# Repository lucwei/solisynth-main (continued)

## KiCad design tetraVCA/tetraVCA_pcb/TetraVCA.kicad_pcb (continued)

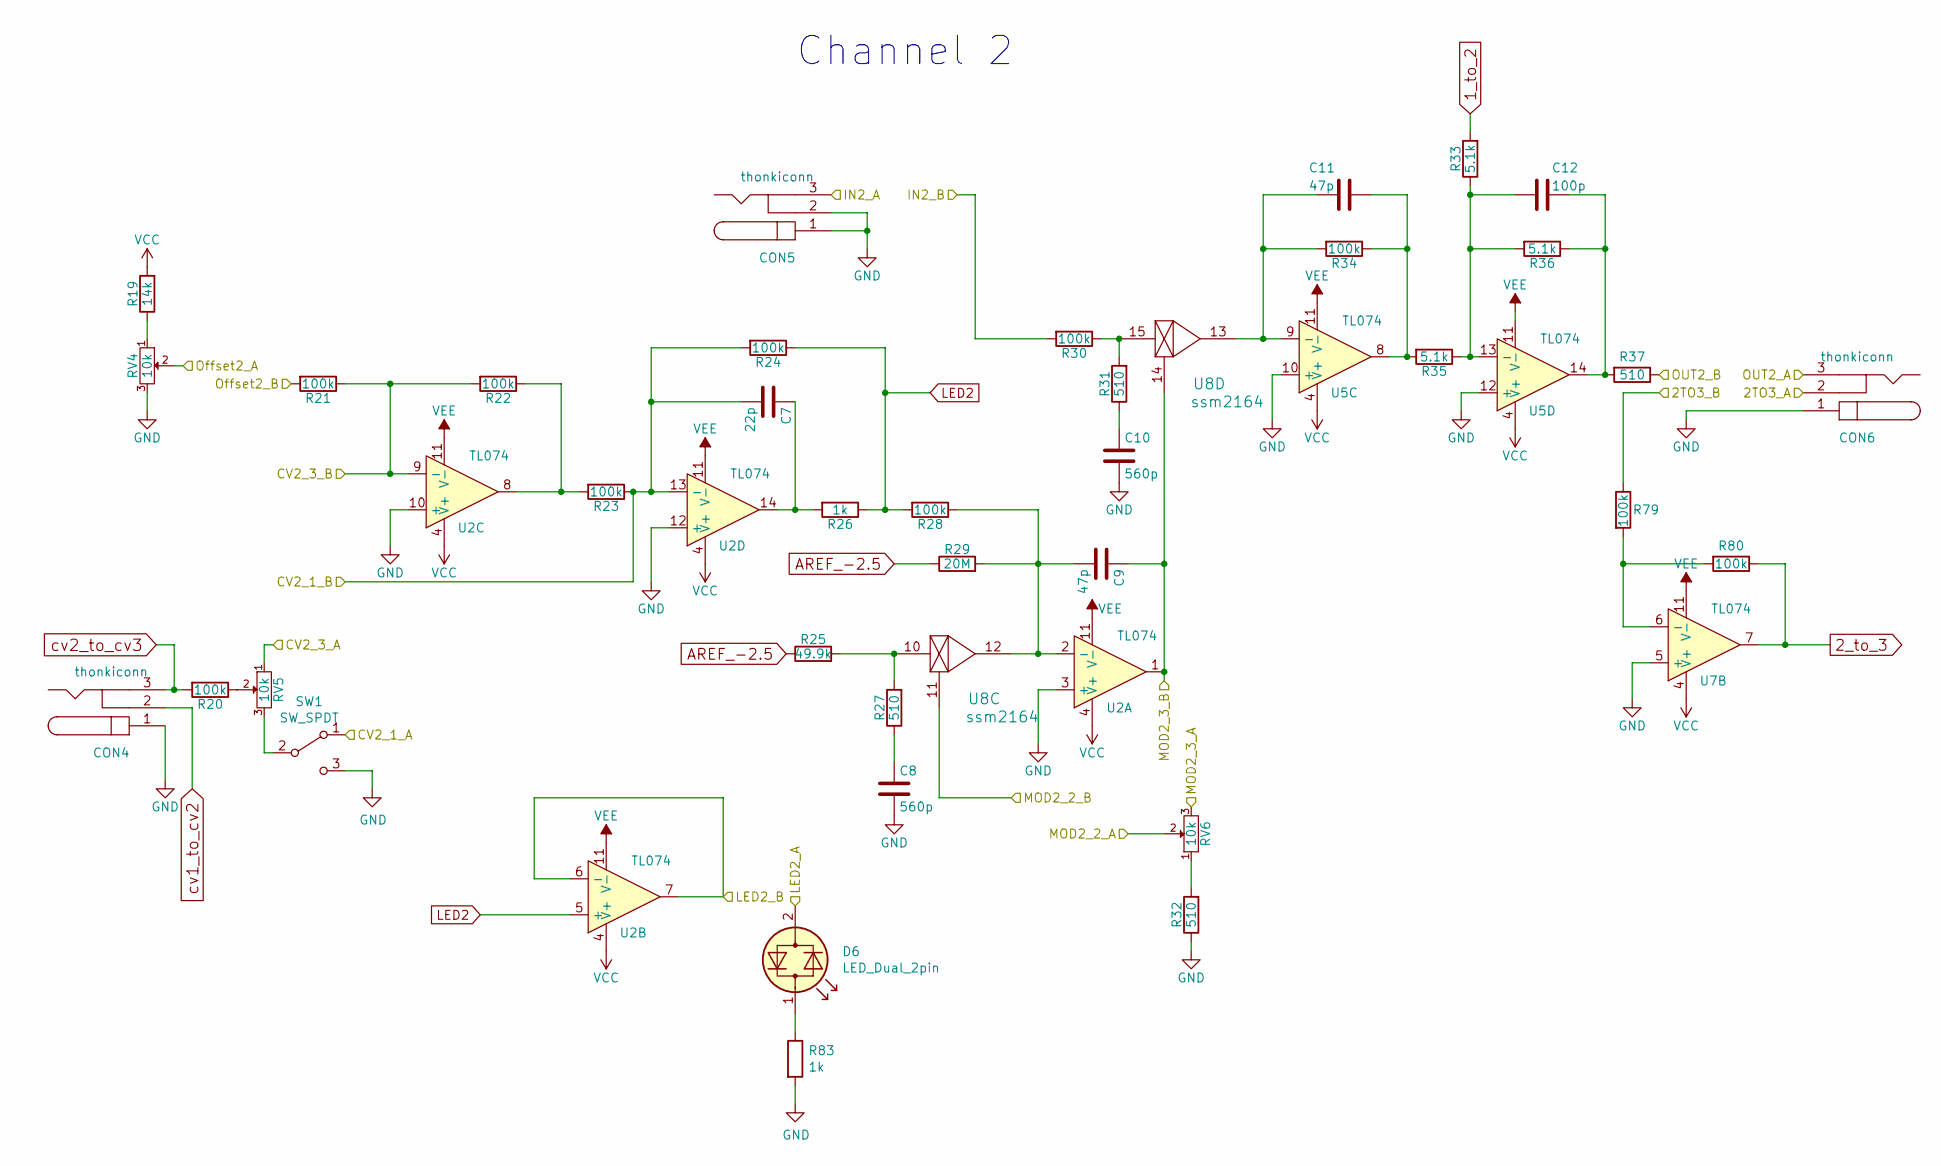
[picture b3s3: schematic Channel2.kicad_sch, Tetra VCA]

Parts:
C7: 22p; C_0603_1608Metric_Pad1.05x0.95mm_HandSolder
C8, C10: 560p; C_0603_1608Metric_Pad1.05x0.95mm_HandSolder
C9, C11: 47p; C_0603_1608Metric_Pad1.05x0.95mm_HandSolder
C12: 100p; C_0603_1608Metric_Pad1.05x0.95mm_HandSolder
CON4, CON5, CON6: thonkiconn; MPN PJ398SM
D6: LED_Dual_2pin; LED_D3.0mm; MPN LTL-10CHJ
R19: 14k; R_0603_1608Metric_Pad1.05x0.95mm_HandSolder
R20, R21, R22, R23, R24, R28, R30, R34, R79, R80: 100k; R_0603_1608Metric_Pad1.05x0.95mm_HandSolder
R25: 49.9k; R_0603_1608Metric_Pad1.05x0.95mm_HandSolder
R26, R83: 1k; R_0603_1608Metric_Pad1.05x0.95mm_HandSolder
R27, R31, R32, R37: 510; R_0603_1608Metric_Pad1.05x0.95mm_HandSolder
R29: 20M; R_0603_1608Metric_Pad1.05x0.95mm_HandSolder
R33, R35, R36: 5.1k; R_0603_1608Metric_Pad1.05x0.95mm_HandSolder
RV4: 10k; Potentiometer_Alps_RK09K_Single_Vertical; MPN RK09L1140A5E
RV5, RV6: 10k; Potentiometer_Alps_RK09K_Single_Vertical; MPN PTV09A-4025U-B103
SW1: SW_SPDT; Switch_EG1249; MPN EG1248
U2, U5, U7: TL074; SOIC-14_3.9x8.7mm_P1.27mm; MPN TL074
U8: ssm2164; SOIC-16_3.9x9.9mm_P1.27mm; MPN SSM2164

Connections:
1_to_2: R33.2; also elsewhere on the board
2TO3_A: CON6.2; also elsewhere on the board
2TO3_B: R79.1; also elsewhere on the board
2_to_3: R80.1, U7.7; also elsewhere on the board
AREF_-2.5: R25.1, R29.1; also elsewhere on the board
CV2_1_A: SW1.1 (A); also elsewhere on the board
CV2_1_B: C7.2, R23.1, R24.2, U2.13 (-); also elsewhere on the board
CV2_3_A: RV5.1; also elsewhere on the board
CV2_3_B: R21.1, R22.2, U2.9 (-); also elsewhere on the board
GND: C8.2, C10.2, CON4.1, CON5.1, CON5.2, CON6.1, R32.1, R83.2, RV4.3, SW1.3 (C), U2.3 (+), U2.10 (+), U2.12 (+), U5.10 (+), U5.12 (+), U7.5 (+); also elsewhere on the board
IN2_A: CON5.3; also elsewhere on the board
IN2_B: R30.2; also elsewhere on the board
LED2: R24.1, R26.1, R28.2, U2.5 (+)
LED2_A: D6.2 (AK); also elsewhere on the board
LED2_B: U2.6 (-), U2.7; also elsewhere on the board
MOD2_2_A: RV6.2; also elsewhere on the board
MOD2_2_B: U8.11; also elsewhere on the board
MOD2_3_A: RV6.3; also elsewhere on the board
MOD2_3_B: C9.1, U2.1, U8.14; also elsewhere on the board
unnamed: C7.1, R26.2, U2.14
unnamed: C8.1, R27.1
unnamed: C9.2, R28.1, R29.2, U2.2 (-), U8.12
unnamed: C10.1, R31.1
unnamed: C11.1, R34.1, R35.2, U5.8
unnamed: C11.2, R34.2, U5.9 (-), U8.13
unnamed: C12.1, R36.1, R37.2, U5.14
unnamed: C12.2, R33.1, R35.1, R36.2, U5.13 (-)
unnamed: D6.1 (KA), R83.1
unnamed: R19.1, RV4.1
unnamed: R20.1, RV5.2
unnamed: R22.1, R23.2, U2.8
unnamed: R25.2, R27.2, U8.10
unnamed: R30.1, R31.2, U8.15
unnamed: R32.2, RV6.1
unnamed: R79.2, R80.2, U7.6 (-)
unnamed: RV5.3, SW1.2 (B)
OUT2_A: CON6.3; also elsewhere on the board
OUT2_B: R37.1; also elsewhere on the board
Offset2_A: RV4.2; also elsewhere on the board
Offset2_B: R21.2; also elsewhere on the board
VCC: R19.2, U2.4 (V+), U5.4 (V+), U7.4 (V+); also elsewhere on the board
VEE: U2.11 (V-), U5.11 (V-), U7.11 (V-); also elsewhere on the board
cv1_to_cv2: CON4.2; also elsewhere on the board
cv2_to_cv3: CON4.3, R20.2; also elsewhere on the board

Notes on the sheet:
Channel 2

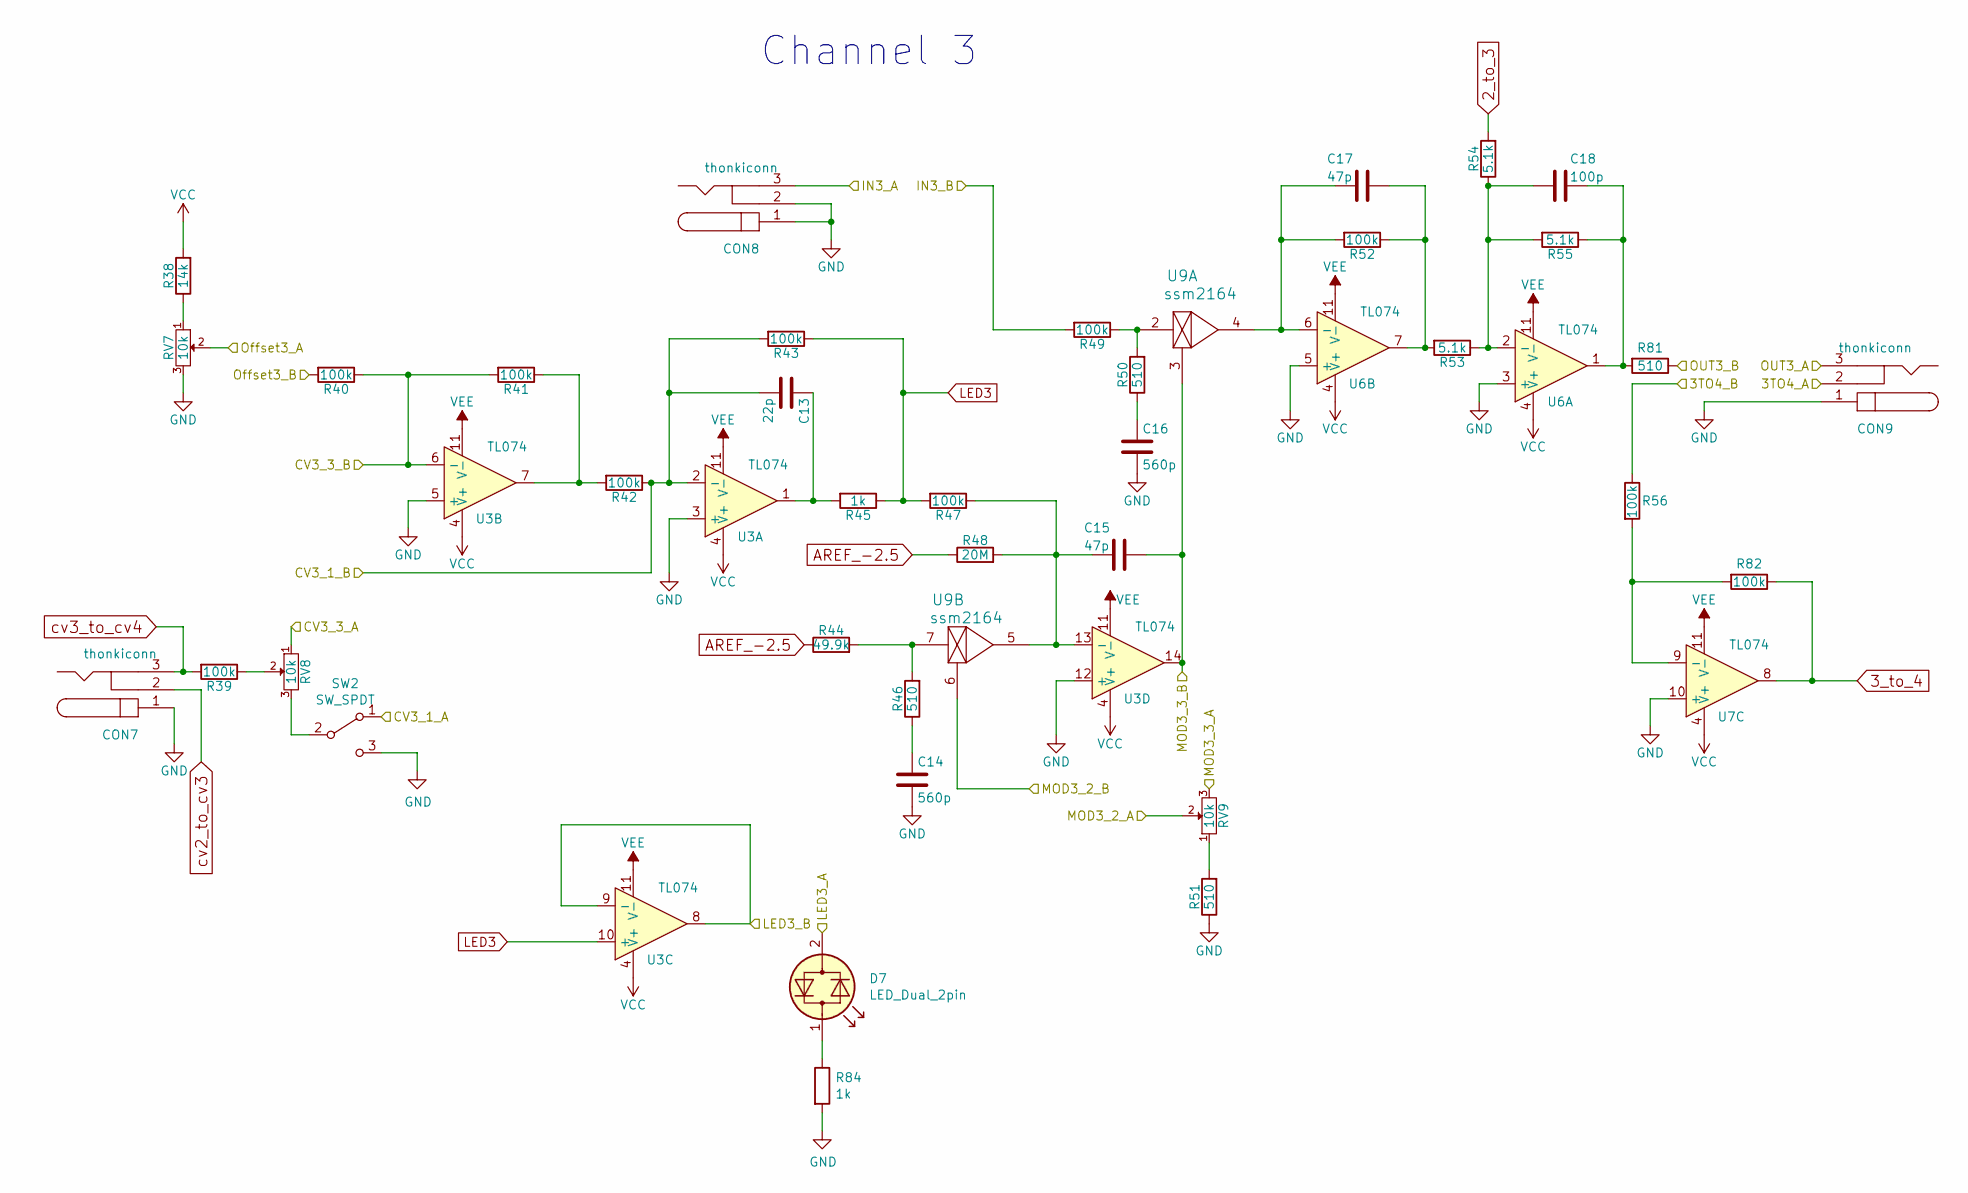
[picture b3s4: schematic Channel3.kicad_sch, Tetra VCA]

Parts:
C13: 22p; C_0603_1608Metric_Pad1.05x0.95mm_HandSolder
C14, C16: 560p; C_0603_1608Metric_Pad1.05x0.95mm_HandSolder
C15, C17: 47p; C_0603_1608Metric_Pad1.05x0.95mm_HandSolder
C18: 100p; C_0603_1608Metric_Pad1.05x0.95mm_HandSolder
CON7, CON8, CON9: thonkiconn; MPN PJ398SM
D7: LED_Dual_2pin; LED_D3.0mm; MPN LTL-10CHJ
R38: 14k; R_0603_1608Metric_Pad1.05x0.95mm_HandSolder
R39, R40, R41, R42, R43, R47, R49, R52, R56, R82: 100k; R_0603_1608Metric_Pad1.05x0.95mm_HandSolder
R44: 49.9k; R_0603_1608Metric_Pad1.05x0.95mm_HandSolder
R45, R84: 1k; R_0603_1608Metric_Pad1.05x0.95mm_HandSolder
R46, R50, R51, R81: 510; R_0603_1608Metric_Pad1.05x0.95mm_HandSolder
R48: 20M; R_0603_1608Metric_Pad1.05x0.95mm_HandSolder
R53, R54, R55: 5.1k; R_0603_1608Metric_Pad1.05x0.95mm_HandSolder
RV7: 10k; Potentiometer_Alps_RK09K_Single_Vertical; MPN RK09L1140A5E
RV8, RV9: 10k; Potentiometer_Alps_RK09K_Single_Vertical; MPN PTV09A-4025U-B103
SW2: SW_SPDT; Switch_EG1249; MPN EG1248
U3, U6, U7: TL074; SOIC-14_3.9x8.7mm_P1.27mm; MPN TL074
U9: ssm2164; SOIC-16_3.9x9.9mm_P1.27mm; MPN SSM2164

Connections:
2_to_3: R54.2; also elsewhere on the board
3TO4_A: CON9.2; also elsewhere on the board
3TO4_B: R56.1; also elsewhere on the board
3_to_4: R82.1, U7.8; also elsewhere on the board
AREF_-2.5: R44.1, R48.1; also elsewhere on the board
CV3_1_A: SW2.1 (A); also elsewhere on the board
CV3_1_B: C13.2, R42.1, R43.2, U3.2 (-); also elsewhere on the board
CV3_3_A: RV8.1; also elsewhere on the board
CV3_3_B: R40.1, R41.2, U3.6 (-); also elsewhere on the board
GND: C14.2, C16.2, CON7.1, CON8.1, CON8.2, CON9.1, R51.1, R84.2, RV7.3, SW2.3 (C), U3.3 (+), U3.5 (+), U3.12 (+), U6.3 (+), U6.5 (+), U7.10 (+); also elsewhere on the board
IN3_A: CON8.3; also elsewhere on the board
IN3_B: R49.2; also elsewhere on the board
LED3: R43.1, R45.1, R47.2, U3.10 (+)
LED3_A: D7.2 (AK); also elsewhere on the board
LED3_B: U3.8, U3.9 (-); also elsewhere on the board
MOD3_2_A: RV9.2; also elsewhere on the board
MOD3_2_B: U9.6; also elsewhere on the board
MOD3_3_A: RV9.3; also elsewhere on the board
MOD3_3_B: C15.1, U3.14, U9.3; also elsewhere on the board
unnamed: C13.1, R45.2, U3.1
unnamed: C14.1, R46.1
unnamed: C15.2, R47.1, R48.2, U3.13 (-), U9.5
unnamed: C16.1, R50.1
unnamed: C17.1, R52.1, R53.2, U6.7
unnamed: C17.2, R52.2, U6.6 (-), U9.4
unnamed: C18.1, R55.1, R81.2, U6.1
unnamed: C18.2, R53.1, R54.1, R55.2, U6.2 (-)
unnamed: D7.1 (KA), R84.1
unnamed: R38.1, RV7.1
unnamed: R39.1, RV8.2
unnamed: R41.1, R42.2, U3.7
unnamed: R44.2, R46.2, U9.7
unnamed: R49.1, R50.2, U9.2
unnamed: R51.2, RV9.1
unnamed: R56.2, R82.2, U7.9 (-)
unnamed: RV8.3, SW2.2 (B)
OUT3_A: CON9.3; also elsewhere on the board
OUT3_B: R81.1; also elsewhere on the board
Offset3_A: RV7.2; also elsewhere on the board
Offset3_B: R40.2; also elsewhere on the board
VCC: R38.2, U3.4 (V+), U6.4 (V+), U7.4 (V+); also elsewhere on the board
VEE: U3.11 (V-), U6.11 (V-), U7.11 (V-); also elsewhere on the board
cv2_to_cv3: CON7.2; also elsewhere on the board
cv3_to_cv4: CON7.3, R39.2; also elsewhere on the board

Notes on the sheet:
Channel 3

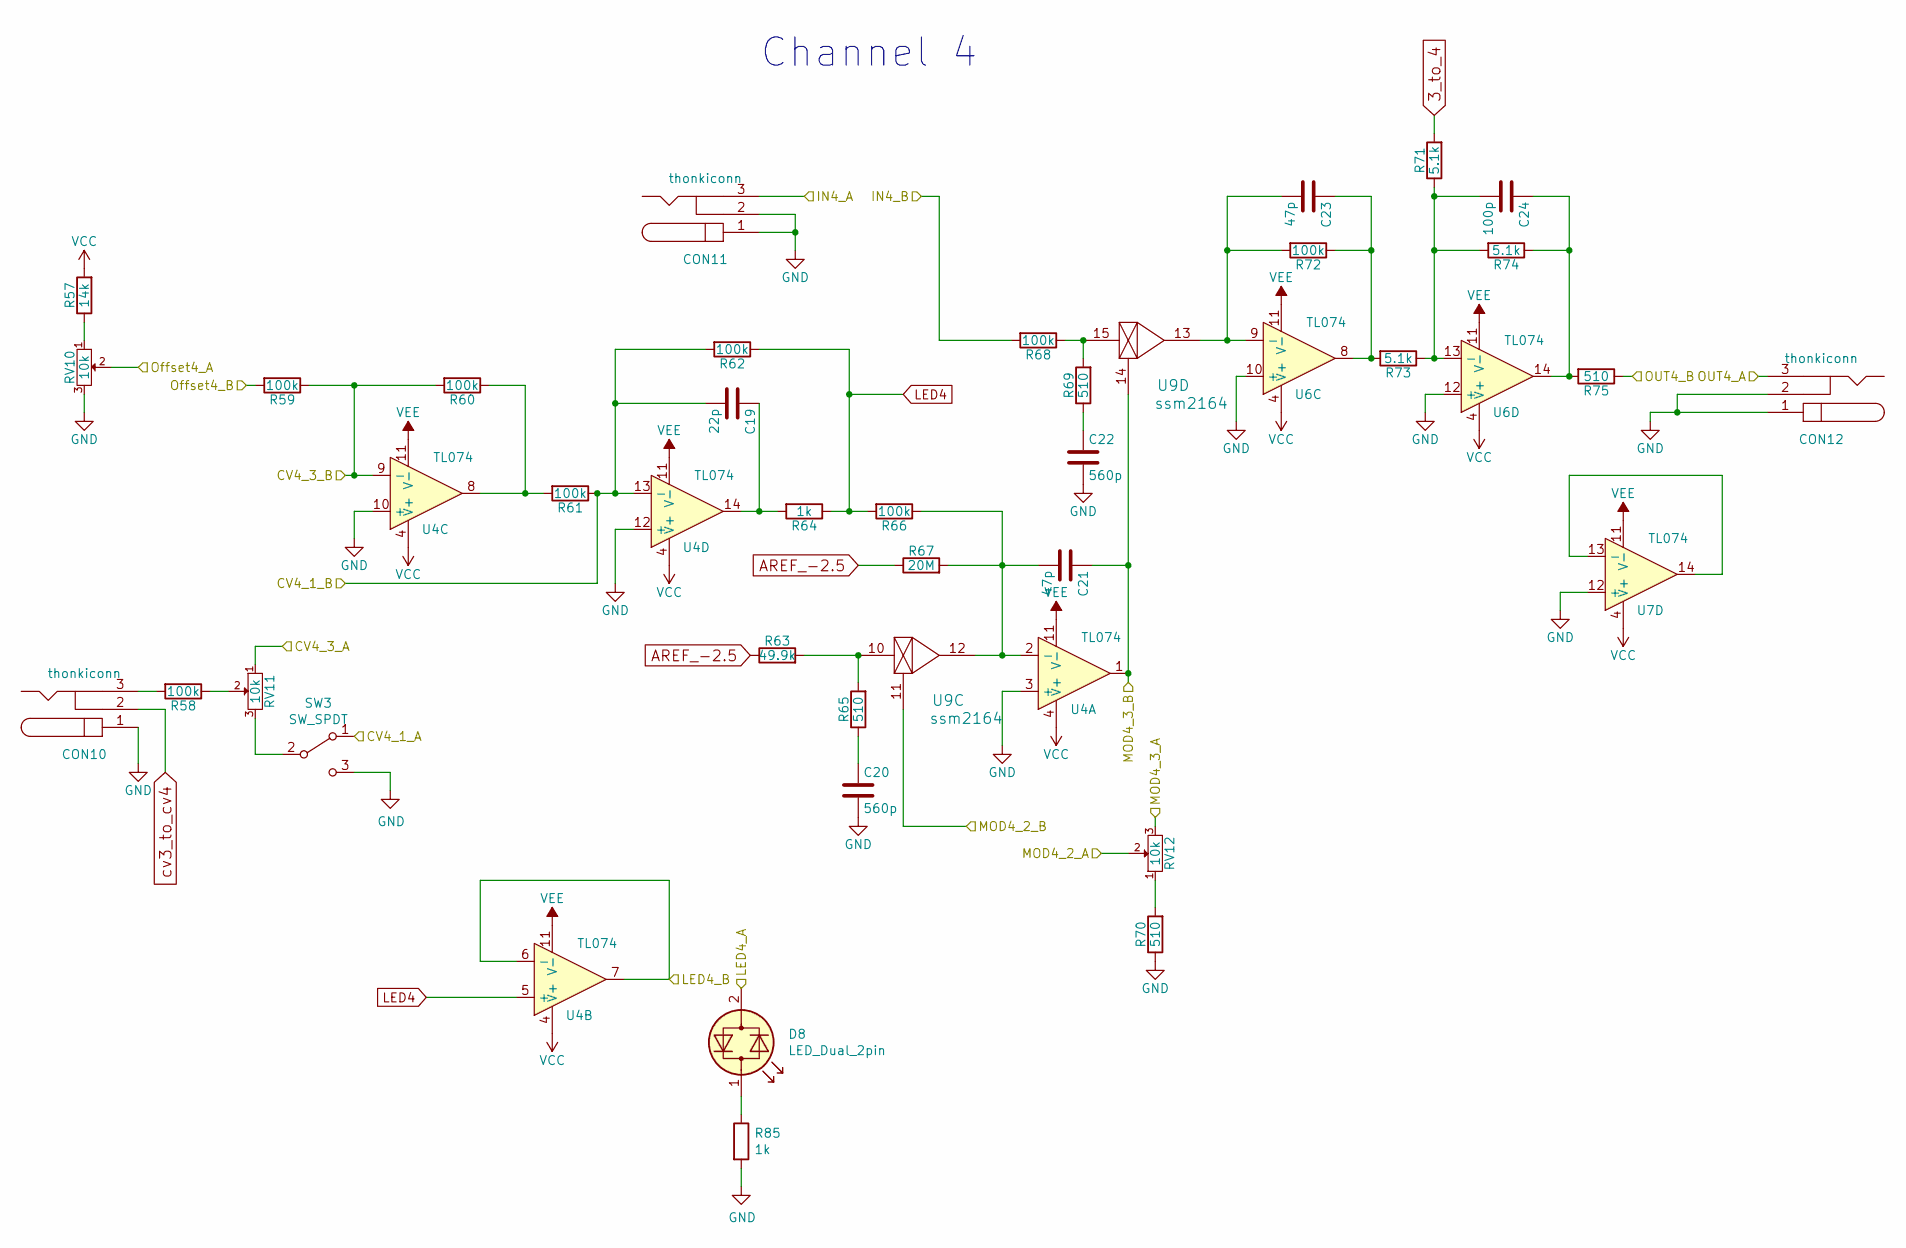
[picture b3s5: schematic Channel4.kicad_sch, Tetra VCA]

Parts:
C19: 22p; C_0603_1608Metric_Pad1.05x0.95mm_HandSolder
C20, C22: 560p; C_0603_1608Metric_Pad1.05x0.95mm_HandSolder
C21, C23: 47p; C_0603_1608Metric_Pad1.05x0.95mm_HandSolder
C24: 100p; C_0603_1608Metric_Pad1.05x0.95mm_HandSolder
CON10, CON11, CON12: thonkiconn; MPN PJ398SM
D8: LED_Dual_2pin; LED_D3.0mm; MPN LTL-10CHJ
R57: 14k; R_0603_1608Metric_Pad1.05x0.95mm_HandSolder
R58, R59, R60, R61, R62, R66, R68, R72: 100k; R_0603_1608Metric_Pad1.05x0.95mm_HandSolder
R63: 49.9k; R_0603_1608Metric_Pad1.05x0.95mm_HandSolder
R64, R85: 1k; R_0603_1608Metric_Pad1.05x0.95mm_HandSolder
R65, R69, R70, R75: 510; R_0603_1608Metric_Pad1.05x0.95mm_HandSolder
R67: 20M; R_0603_1608Metric_Pad1.05x0.95mm_HandSolder
R71, R73, R74: 5.1k; R_0603_1608Metric_Pad1.05x0.95mm_HandSolder
RV10: 10k; Potentiometer_Alps_RK09K_Single_Vertical; MPN RK09L1140A5E
RV11, RV12: 10k; Potentiometer_Alps_RK09K_Single_Vertical; MPN PTV09A-4025U-B103
SW3: SW_SPDT; Switch_EG1249; MPN EG1248
U4, U6, U7: TL074; SOIC-14_3.9x8.7mm_P1.27mm; MPN TL074
U9: ssm2164; SOIC-16_3.9x9.9mm_P1.27mm; MPN SSM2164

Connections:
3_to_4: R71.2; also elsewhere on the board
AREF_-2.5: R63.1, R67.1; also elsewhere on the board
CV4_1_A: SW3.1 (A); also elsewhere on the board
CV4_1_B: C19.2, R61.1, R62.2, U4.13 (-); also elsewhere on the board
CV4_3_A: RV11.1; also elsewhere on the board
CV4_3_B: R59.1, R60.2, U4.9 (-); also elsewhere on the board
GND: C20.2, C22.2, CON10.1, CON11.1, CON11.2, CON12.1, CON12.2, R70.1, R85.2, RV10.3, SW3.3 (C), U4.3 (+), U4.10 (+), U4.12 (+), U6.10 (+), U6.12 (+), U7.12 (+); also elsewhere on the board
IN4_A: CON11.3; also elsewhere on the board
IN4_B: R68.2; also elsewhere on the board
LED4: R62.1, R64.1, R66.2, U4.5 (+)
LED4_A: D8.2 (AK); also elsewhere on the board
LED4_B: U4.6 (-), U4.7; also elsewhere on the board
MOD4_2_A: RV12.2; also elsewhere on the board
MOD4_2_B: U9.11; also elsewhere on the board
MOD4_3_A: RV12.3; also elsewhere on the board
MOD4_3_B: C21.1, U4.1, U9.14; also elsewhere on the board
unnamed: C19.1, R64.2, U4.14
unnamed: C20.1, R65.1
unnamed: C21.2, R66.1, R67.2, U4.2 (-), U9.12
unnamed: C22.1, R69.1
unnamed: C23.1, R72.1, R73.2, U6.8
unnamed: C23.2, R72.2, U6.9 (-), U9.13
unnamed: C24.1, R74.1, R75.2, U6.14
unnamed: C24.2, R71.1, R73.1, R74.2, U6.13 (-)
unnamed: CON10.3, R58.2
unnamed: D8.1 (KA), R85.1
unnamed: R57.1, RV10.1
unnamed: R58.1, RV11.2
unnamed: R60.1, R61.2, U4.8
unnamed: R63.2, R65.2, U9.10
unnamed: R68.1, R69.2, U9.15
unnamed: R70.2, RV12.1
unnamed: RV11.3, SW3.2 (B)
unnamed: U7.13 (-), U7.14
OUT4_A: CON12.3; also elsewhere on the board
OUT4_B: R75.1; also elsewhere on the board
Offset4_A: RV10.2; also elsewhere on the board
Offset4_B: R59.2; also elsewhere on the board
VCC: R57.2, U4.4 (V+), U6.4 (V+), U7.4 (V+); also elsewhere on the board
VEE: U4.11 (V-), U6.11 (V-), U7.11 (V-); also elsewhere on the board
cv3_to_cv4: CON10.2; also elsewhere on the board

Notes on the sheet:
Channel 4

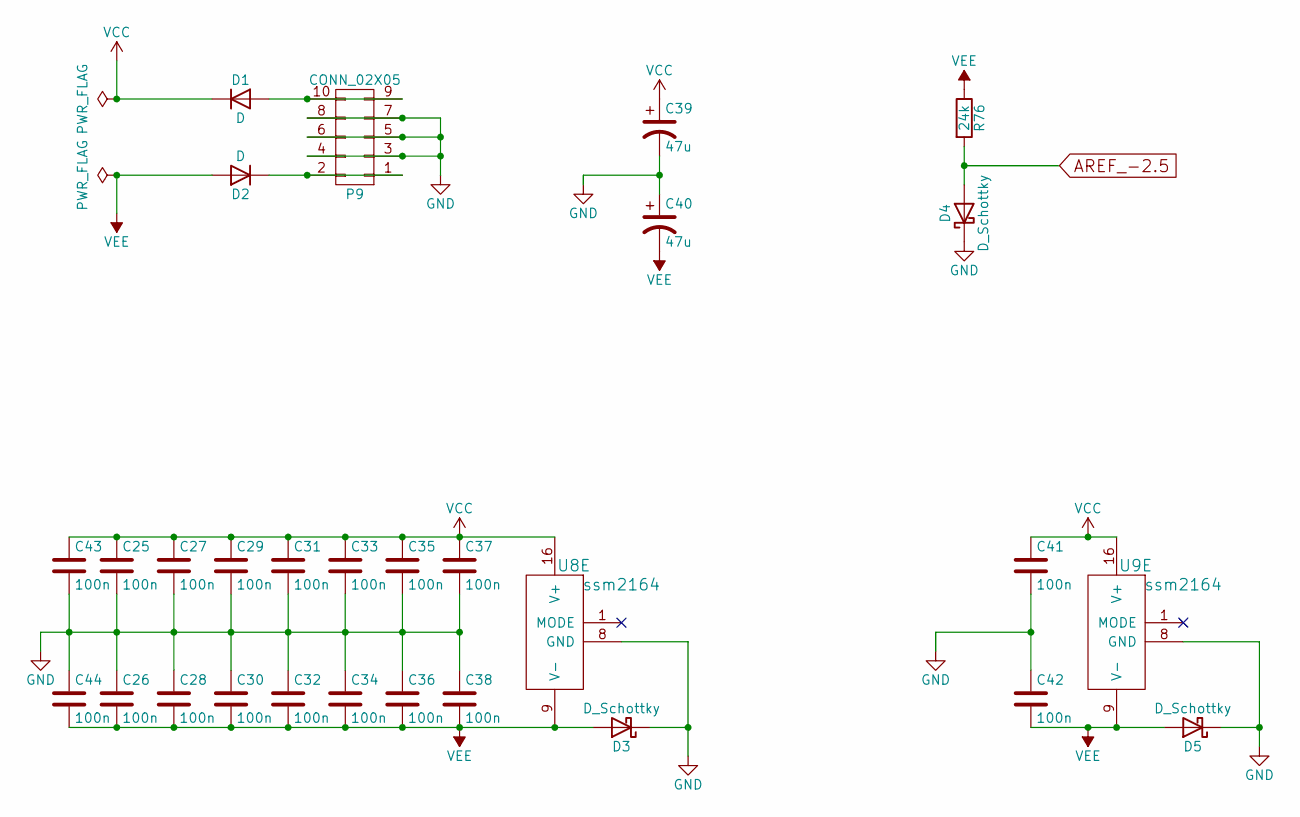
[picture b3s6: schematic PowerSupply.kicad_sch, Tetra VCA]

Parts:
C25, C26, C27, C28, C29, C30, C31, C32, C33, C34, C35, C36, C37, C38, C41, C42, C43, C44: 100n; C_0603_1608Metric_Pad1.05x0.95mm_HandSolder
C39, C40: 47u; CP_Elec_6.3x5.3
D1, D2: D; D_0603_1608Metric_Pad1.05x0.95mm_HandSolder
D3, D5: D_Schottky; D_0603_1608Metric_Pad1.05x0.95mm_HandSolder
D4: D_Schottky; TSOT-23; MPN LM4040CYM3-2.5-TR
P9: CONN_02X05; IDC-Header_2x05_P2.54mm_Vertical; MPN 61201021621
R76: 24k; R_0603_1608Metric_Pad1.05x0.95mm_HandSolder
U8, U9: ssm2164; SOIC-16_3.9x9.9mm_P1.27mm; MPN SSM2164

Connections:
AREF_-2.5: D4.2 (A), R76.2; also elsewhere on the board
GND: C25.2, C26.1, C27.2, C28.1, C29.2, C30.1, C31.2, C32.1, C33.2, C34.1, C35.2, C36.1, C37.2, C38.1, C39.2, C40.1, C41.2, C42.1, C43.2, C44.1, D3.1 (K), D4.1 (K), D5.1 (K), P9.3, P9.4, P9.5, P9.6, P9.7, P9.8, U8.8 (GND), U9.8 (GND); also elsewhere on the board
unnamed: D1.2 (A), P9.9, P9.10
unnamed: D2.1 (K), P9.1, P9.2
VCC: C25.1, C27.1, C29.1, C31.1, C33.1, C35.1, C37.1, C39.1, C41.1, C43.1, D1.1 (K), U8.16 (V+), U9.16 (V+); also elsewhere on the board
VEE: C26.2, C28.2, C30.2, C32.2, C34.2, C36.2, C38.2, C40.2, C42.2, C44.2, D2.2 (A), D3.2 (A), D5.2 (A), R76.1, U8.9 (V-), U9.9 (V-); also elsewhere on the board

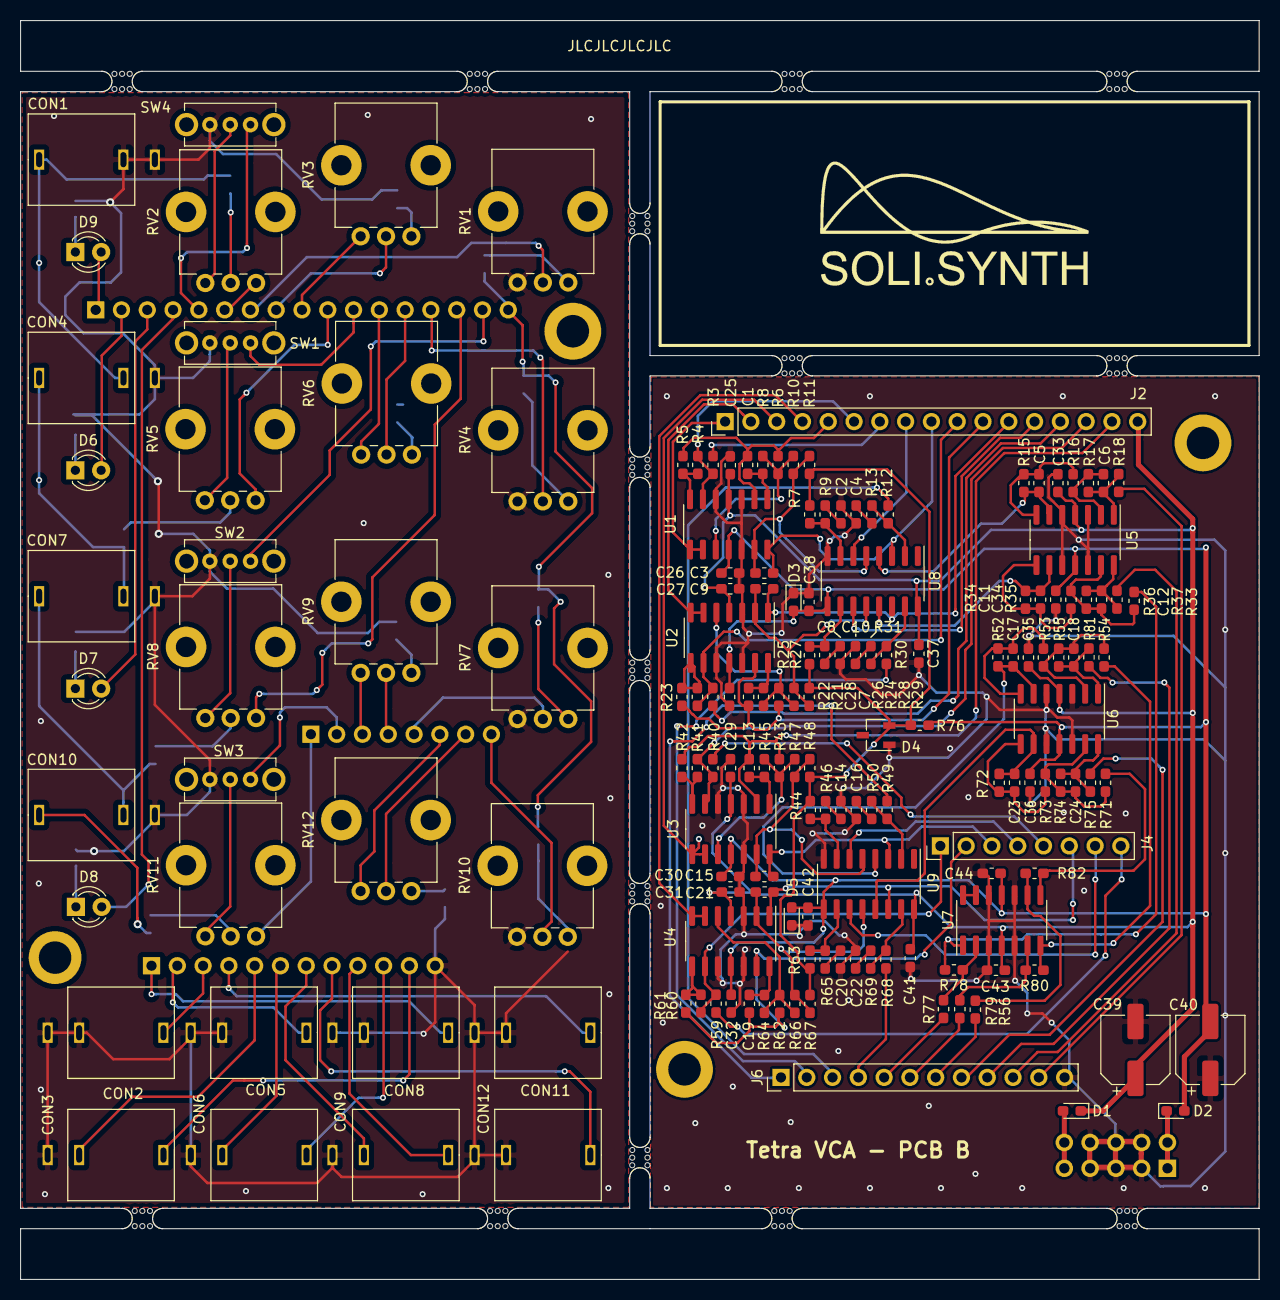
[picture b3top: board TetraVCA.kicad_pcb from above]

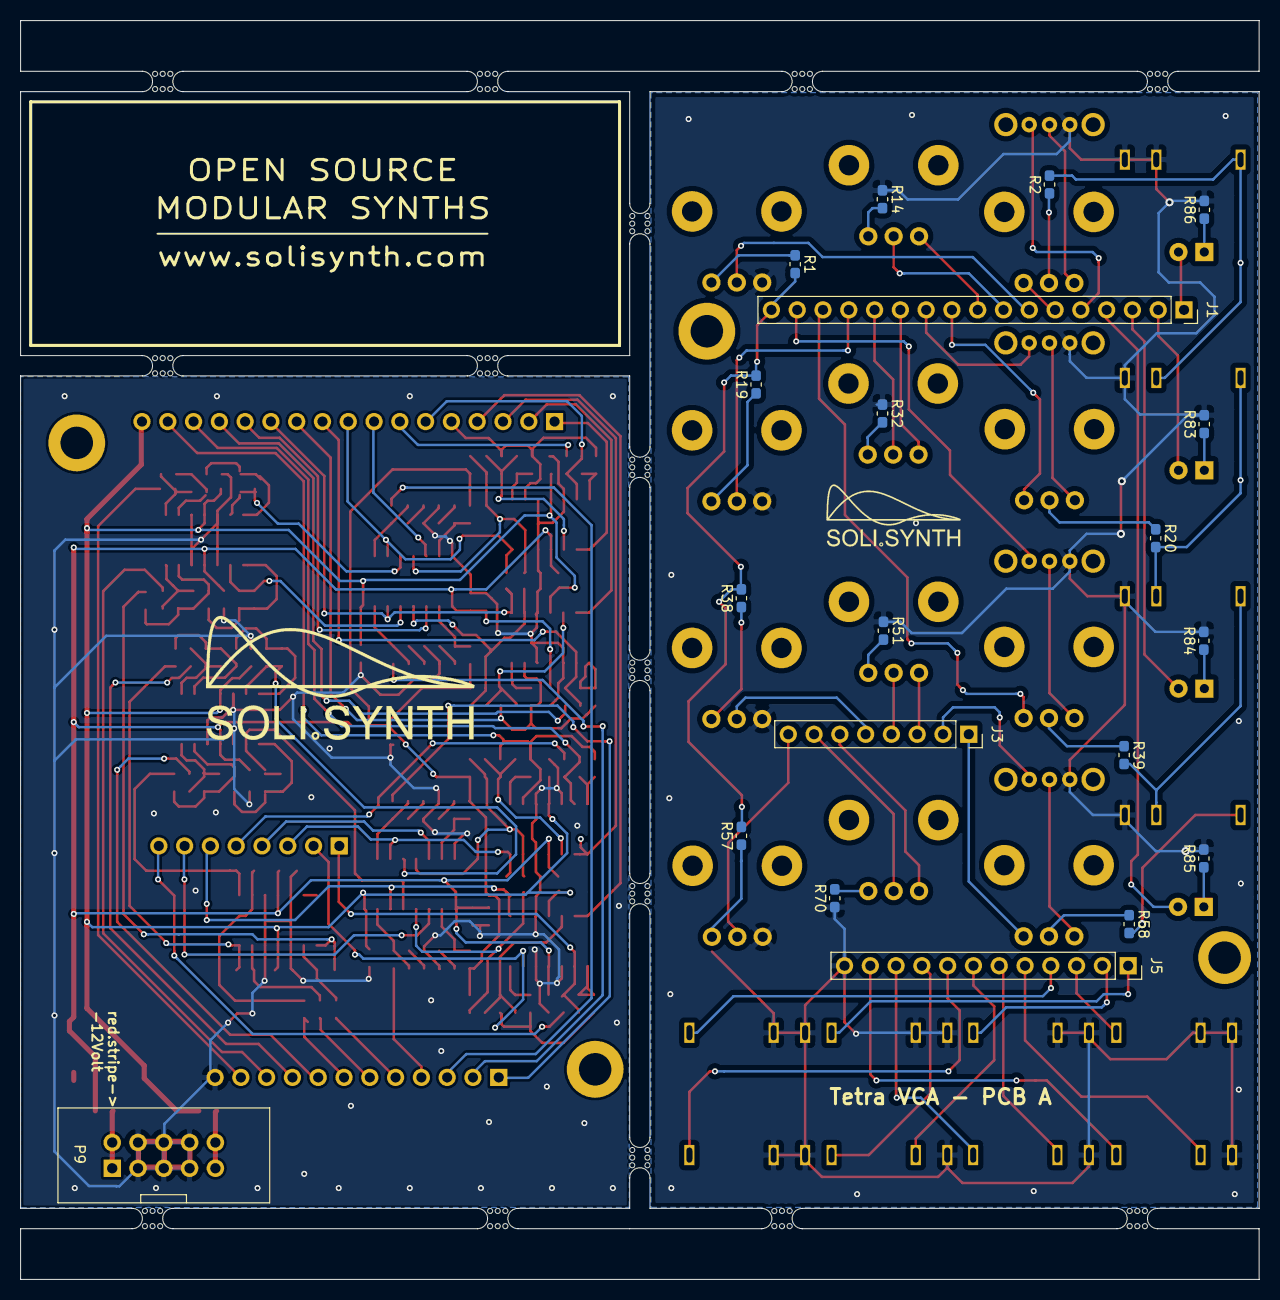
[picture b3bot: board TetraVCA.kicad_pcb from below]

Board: 2 copper layers, 122.0 x 124.0 mm, 198 parts (20 on the bottom side), 155 nets.

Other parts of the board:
mouse-bite-2mm-slot, mouse-bite-2mm-slot#2, mouse-bite-2mm-slot#3, mouse-bite-2mm-slot#4, mouse-bite-2mm-slot#5, mouse-bite-2mm-slot#6, mouse-bite-2mm-slot#7, mouse-bite-2mm-slot#8, mouse-bite-2mm-slot#9, mouse-bite-2mm-slot#10, mouse-bite-2mm-slot#11, mouse-bite-2mm-slot#12, mouse-bite-2mm-slot#13, mouse-bite-2mm-slot#14, mouse-bite-2mm-slot#15: VAL**; mouse-bite-2mm-slot

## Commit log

2023-01-18 adds DS_Store file to gitignore
2023-01-18 adds kicad6 temporary files
2023-01-21 adds schematic page comments
2023-01-21 adds bom folder with ibom.html file
2023-01-21 removes wrong partnumber of PTC thermistor
2023-01-21 adds bom spreadsheet
2023-01-21 removing spreadsheet files from gitignore
2023-01-21 consolidating diodes
2023-01-21 changing all diodes to same type
2023-01-21 consolidating 20k res
2023-01-21 removes ods and adds csv bom file
2023-01-21 removing xml bom file
2023-01-23 adding stereoMixer bom spreadsheet
2023-02-02 chaging 1M to 30k for triangle adjustment
2023-02-02 updated BOM
2023-02-04 changing R37 from 1M to 2M2 to get lower minimal frequency
2023-02-04 final minor value changes
2023-02-04 part values updates
